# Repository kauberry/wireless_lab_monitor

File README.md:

## Wireless Lab Monitor ##
A simple MySensors-based, network-connected telemetry device for monitoring status of equipment in a biological laboratory setting.

### Rationale ###
Biological experiments are important. Biological experiments are sensitive to changes in temperature, humidity, and lots of other things. Let's use a bit of IoT technology for good instead of evil, shall we?

This initial prototype sensor will look after things like incubators and autoclaves to take note of the status of their doors and temperatures in an effort to keep their contents safe and viable.

### System Design ###
The sensors will communicate through a [MySensors](https://www.mysensors.org)-based gateway running on a [Raspberry Pi Model 3](https://www.raspberrypi.org/products/raspberry-pi-3-model-b/). This gateway box then sends the gathered telemetry data to a server via the [MQTT](http://mqtt.org) protocol where it is stored in a local database and presented through a web interface and a corresponding RESTful API.

### Hardware Description - Single Item Sensor ###
The prototype uses a standard surface mount [Microchip/Atmel ATmega328p](https://www.microchip.com/wwwproducts/en/ATMEGA328P) in a TQFP32 package, coupled with a [Nordic Semiconductor nRF24L01 Tranceiver](https://www.nordicsemi.com/eng/Products/2.4GHz-RF/nRF24L01P) to communicate with the aforementional backend server. Sensor hardware includes temperature sensors ([Dallas/Maxim DS18b20 Digital Thermometer](https://www.maximintegrated.com/en/products/analog/sensors-and-sensor-interface/DS18B20.html)) along with Hall-effect-based position sensors ([Allegro A1104](https://www.allegromicro.com/en/Products/Magnetic-Digital-Position-Sensor-ICs/Hall-Effect-Unipolar-Switches/A1101-2-3-4-6.aspx) or similar) for door open/closed status detection. Jacks are provided to add external versions of the same sensors if placement is an issue.

#### Parts Manifest ####

|Quantity | Value         |        Name        |        Package|
|-------: | ------------- | :----------------: | -------------:|
|       1 | ATMEGA328P-AU |   Microprocessor   |           TQFP|
|       2 | 10uF          |    Tantalum Cap    |           1206|
|       4 | 0.1uF         |     Capacitor      |           0805|
|       1 | green         |        LED         |           0603|
|       3 | 10kΩ          |      Resistor      |           0805|
|       1 | 4.7kΩ         |      Resistor      |           0805|
|       1 | 220Ω          |      Resistor      |           0805|
|       1 | CR2032        |   Battery Holder   ||
|       1 | 2.5mm         |     Audio Jack     |         PJ-242|
|       1 | 3.5mm         |     Audio Jack     |         PJ-328|
|       1 |               |     SMT Switch     ||
|       1 |               | Temperature Sensor |        DS18B20|
|       1 |               | Hall-Effect Sensor |          A3144|
|       1 | 1x6           |     Pin Header     | FTDI Interface|
|       1 | NRF24         |       Radio        |       Mini SMT|

#### Layout ####

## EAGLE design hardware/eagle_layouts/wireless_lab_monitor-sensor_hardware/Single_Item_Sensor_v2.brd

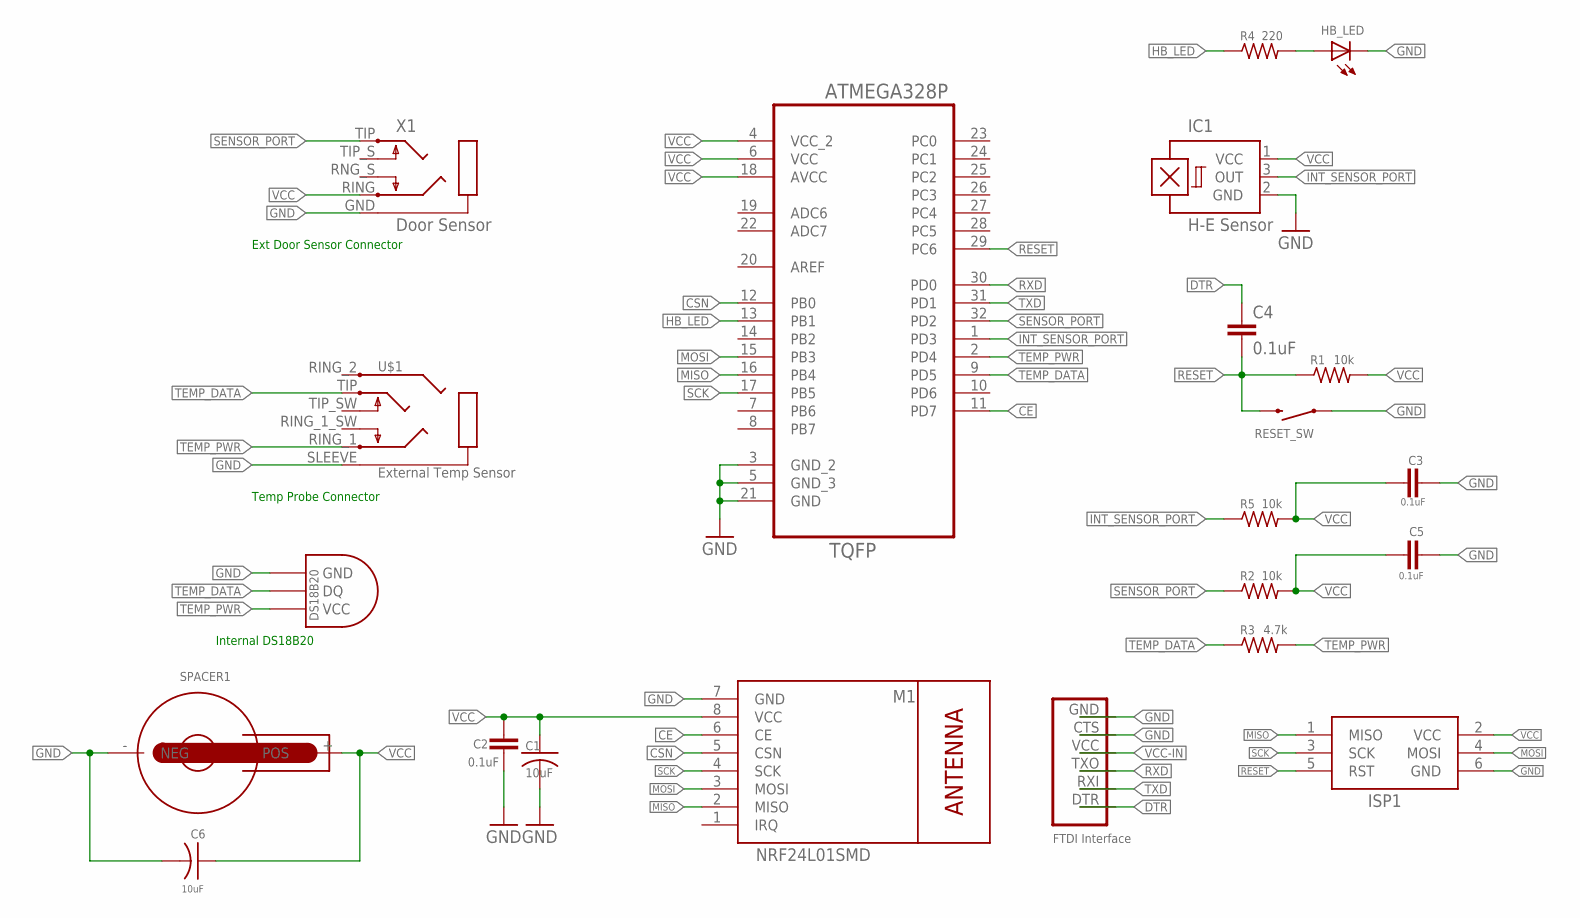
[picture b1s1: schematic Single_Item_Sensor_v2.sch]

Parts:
C1, C6: 10uF; C1206
C2, C3, C4, C5: 0.1uF; 0805
HB_LED: LEDCHIP-LED0603; CHIP-LED0603
IC1: H-E Sensor; SIP3-UA
ISP1: AVRISP-6; AVRISP
M1: NRF24L01SMD; WIRELESS-NRF24L01-SMD
R1, R2, R5: 10k; M0805
R3: 4.7k; M0805
R4: 220; M0805
RESET_SW: Reset; TACTILE-SWITCH-1101NE
SPACER1: WA-BCPH_SMT_79527141; 79527141
U1: ATMEGA328P-AU; QFP80P900X900X120-32N
U$1: External Temp Sensor; PJ-242
U$2: DS1820TO92; DS1820
U$3: FTDI Interface; 1X6-FTDI
X1: Door Sensor; PG203J

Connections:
CE: M1.6 (CE), U1.11 (PD7)
CSN: M1.5 (CSN), U1.12 (PB0)
DTR: C4.1, U$3.DTR
GND: C1.2, C2.2, C3.2, C5.2, C6.2, HB_LED.C, IC1.2 (GND), ISP1.6 (GND), M1.7 (GND), RESET_SW.P$1 (1), SPACER1.- (NEG), U1.3 (GND_2), U1.5 (GND_3), U1.21 (GND), U$1.SLEEVE (5), U$2.GND, U$3.CTS, U$3.GND, X1.GND (1)
HB_LED: R4.1, U1.13 (PB1)
INT_SENSOR_PORT: IC1.3 (OUT), R5.1, U1.1 (PD3)
LED+: HB_LED.A, R4.2
MISO: ISP1.1 (MISO), U1.16 (PB4)
MOSI: ISP1.4 (MOSI), U1.15 (PB3)
RESET: C4.2, ISP1.5 (RST), R1.1, RESET_SW.P$2 (2), U1.29 (PC6)
RXD: U1.30 (PD0), U$3.TXO
SCK: ISP1.3 (SCK), U1.17 (PB5)
SENSOR_PORT: R2.1, U1.32 (PD2), X1.TIP (5)
TEMP_DATA: R3.1, U1.9 (PD5), U$1.TIP (6), U$2.DQ
TEMP_PWR: R3.2, U1.2 (PD4), U$1.RING_1 (3), U$2.VDD (VCC)
TXD: U1.31 (PD1), U$3.RXI
VCC: C1.1, C2.1, C3.1, C5.1, C6.1, IC1.1 (VCC), ISP1.2 (VCC), M1.8 (VCC), R1.2, R2.2, R5.2, SPACER1.+ (POS), U1.4 (VCC_2), U1.6 (VCC), U1.18 (AVCC), X1.RING (2)
VCC-IN: U$3.VCC

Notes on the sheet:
Internal DS18B20
Temp Probe Connector
Ext Door Sensor Connector

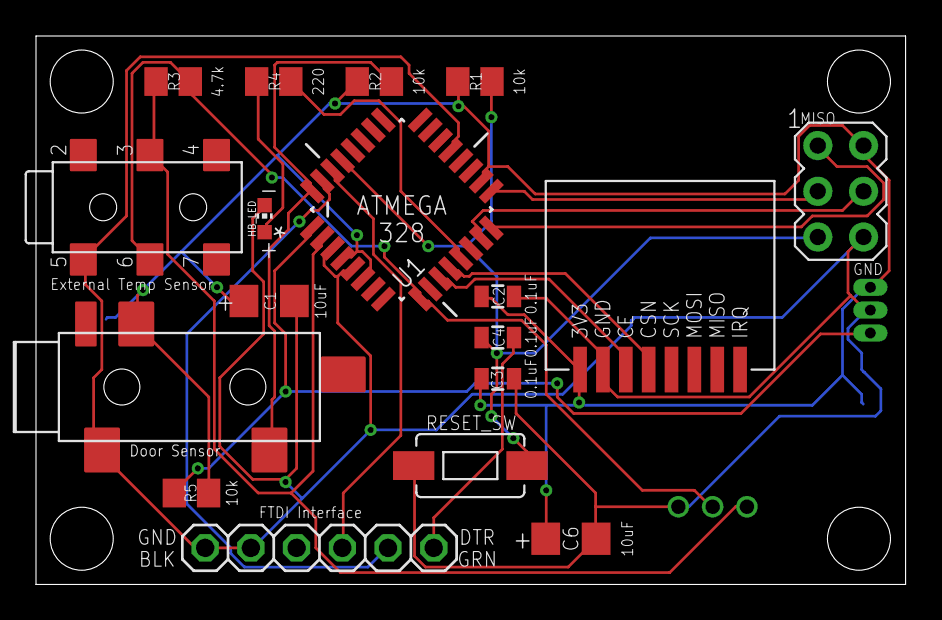
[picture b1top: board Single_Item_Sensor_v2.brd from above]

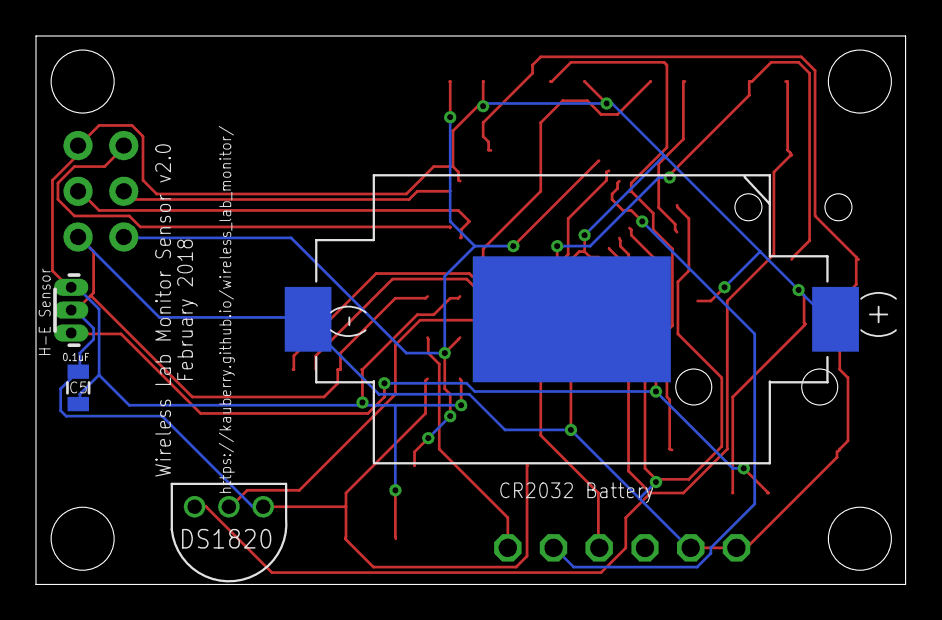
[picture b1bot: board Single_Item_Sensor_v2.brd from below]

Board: 2 copper layers, 48.3 x 30.5 mm, 22 parts (4 on the bottom side), 17 nets.

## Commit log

2018-01-06 Initial hardware commit
2018-01-06 Starting documentation folder
2018-01-06 Set theme jekyll-theme-tactile
2018-01-06 Testing pages functionality
2018-01-06 Adding initial readme file
2018-01-06 renaming index file
2018-01-06 Adding README file
2018-02-07 Moving things around for better consistency
2018-02-07 Updating README file
2018-02-07 README update
2018-02-07 Increasing inline picture widths
2018-02-07 Initial commit of single item sensor firmware code
2018-02-07 README file update with parts manifest
2018-02-08 Parts manifest table fix
2018-02-10 Adding v2 hardware designs
2018-02-10 Updating board specification files
2018-02-10 First working version using the NodeManager package from MySensors
2018-02-13 Updating Sketchup files
2018-02-17 Changing over to 1MHz clock and correctly assigning the CS and CE pins for the radio
2018-03-07 More cleanup on the firmware code
2018-03-10 Fixing config values to disable non-functional signal level reporting
2018-04-17 Working version with NodeManager 1.6
2018-05-18 Working 1.7 based version

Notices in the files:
parts and their libraries:
EAGLE-BATTERY_HOLDERS-rev16b: Copyright: Würth Elektronik
